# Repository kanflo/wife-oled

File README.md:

**Wife OLED**
==========

I wanted a display showing the current outside temperature alongside with the forecasted temperature in 8 hours.

The device subscribes to the topics `home/temperature/outside` and `home/temperature/forecast` displaying them in the left and right part of the display respectively. For readability I use a large font, [Ubuntu Condensed](http://font.ubuntu.com/#charset-condensed) in sizes 32px and 28px.

**Building**

Clone this repo:

```
git clone https://github.com/kanflo/wife-oled.git
cd wife-oled
git submodule init && git submodule update

```

Set the SSID configuration of EOR by adding the following to the file ```esp-open-rtos/include/private_ssid_config.h```:

```
#define WIFI_SSID "my ssid"
#define WIFI_PASS "my password"
```

Configure the MQTT stuff in ```mqtt_config.h```

Now ```make``` and ```make flash```

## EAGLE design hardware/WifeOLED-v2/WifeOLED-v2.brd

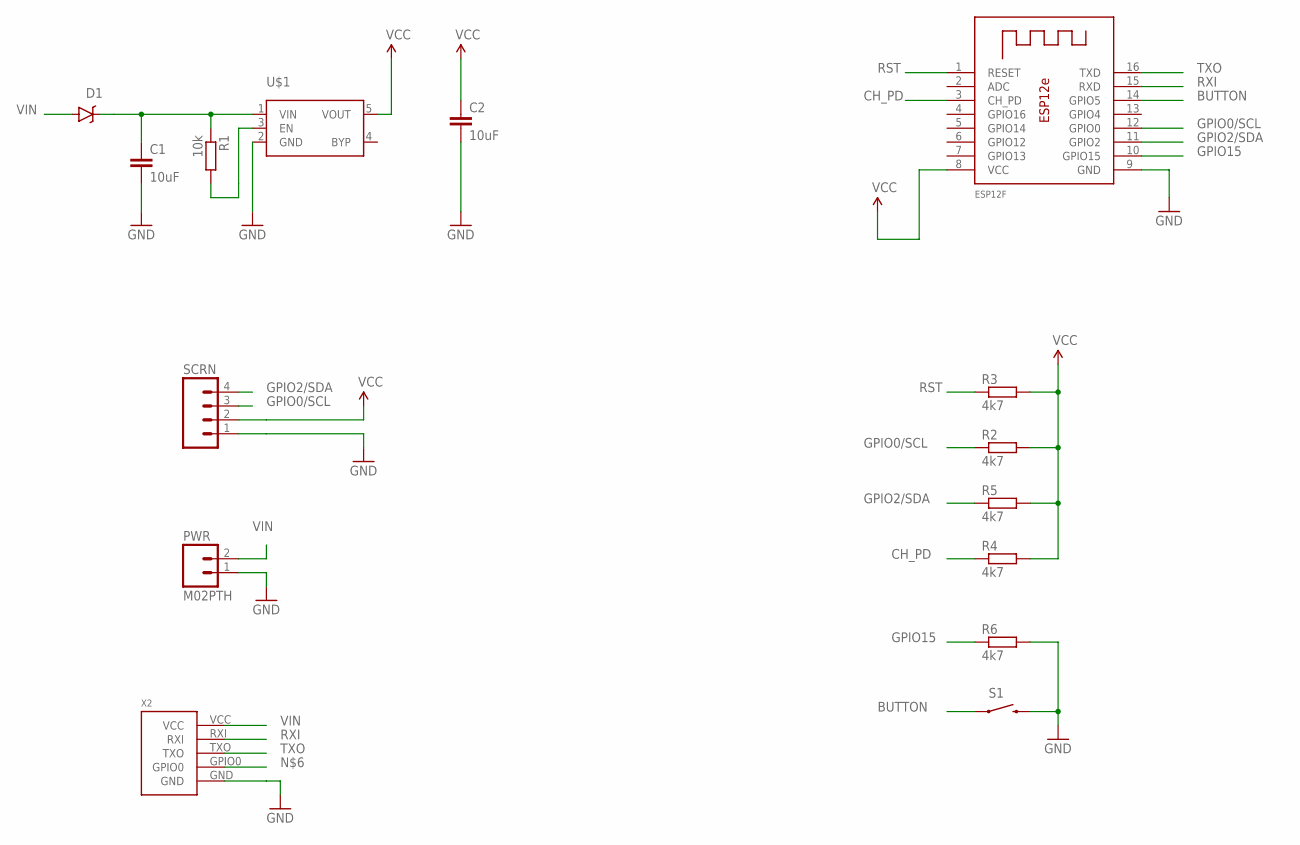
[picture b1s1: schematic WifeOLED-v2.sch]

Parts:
C1, C2: 10uF; 0603-CAP
D1: DIODE-SCHOTTKYSOD-123FL; SOD-123FL
ESP12F: ESP-12E
PWR: M02PTH; 1X02
R1: 10k; R0603
R2, R3, R4, R5, R6: 4k7; R0603
S1: SWITCH-MOMENTARY-2SMD-1101NE; TACTILE-SWITCH-1101NE
SCRN: M04PTH; 1X04
U$1: SPX3819; SOT23-5
X2: ESPROGESPROG-DEVICE; ESPROG

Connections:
BUTTON: ESP12F.14 (GPIO5), S1.1
CH_PD: ESP12F.3 (CH_PD), R4.1
GND: C1.2, C2.2, ESP12F.9 (GND), PWR.1, R6.2, S1.2, SCRN.1, U$1.2 (GND), X2.GND
GPIO0/SCL: ESP12F.12 (GPIO0), R2.1, SCRN.3
GPIO2/SDA: ESP12F.11 (GPIO2), R5.1, SCRN.4
GPIO15: ESP12F.10 (GPIO15), R6.1
unnamed: R1.2, U$1.3 (EN)
unnamed: C1.1, D1.C, R1.1, U$1.1 (VIN)
RST: ESP12F.1 (RESET), R3.1
RXI: ESP12F.15 (RXD), X2.RXI
TXO: ESP12F.16 (TXD), X2.TXO
VCC: C2.1, ESP12F.8 (VCC), R2.2, R3.2, R4.2, R5.2, SCRN.2, U$1.5 (VOUT)
VIN: D1.A, PWR.2, X2.VCC

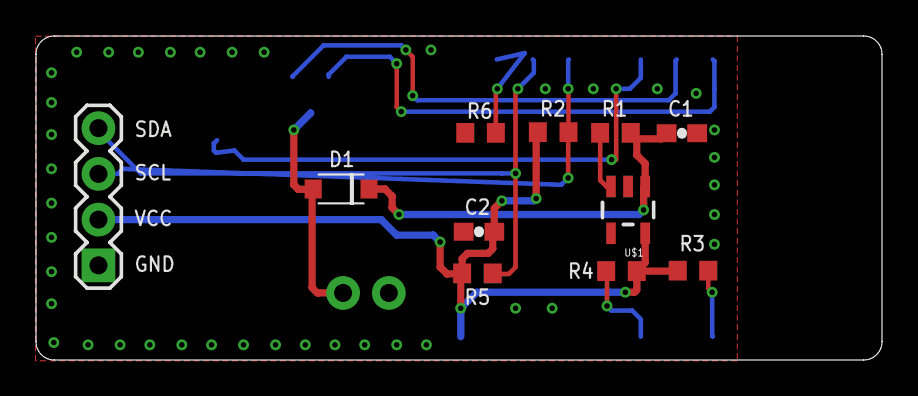
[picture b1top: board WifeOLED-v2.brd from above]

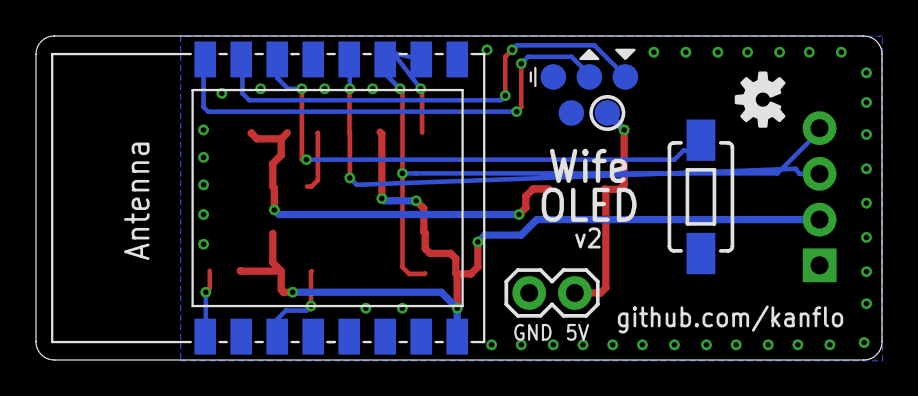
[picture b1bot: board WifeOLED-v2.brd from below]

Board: 2 copper layers, 47.0 x 18.0 mm, 16 parts (5 on the bottom side), 13 nets.

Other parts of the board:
U$2: OSHW-LOGO-S

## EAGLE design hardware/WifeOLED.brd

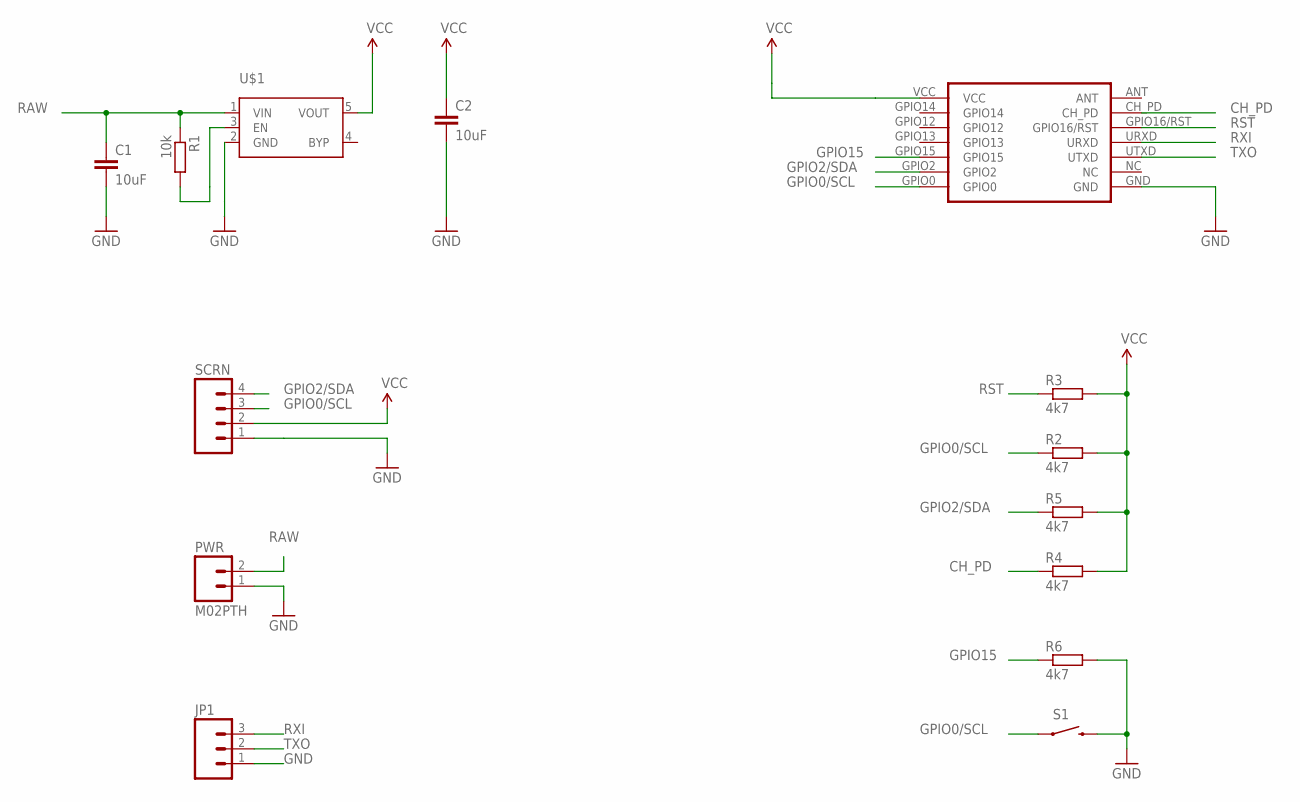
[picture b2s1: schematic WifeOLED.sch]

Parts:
C1, C2: 10uF; 0603-CAP
ESP-1: ESP-03
JP1: M03PTH; 1X03
PWR: M02PTH; 1X02
R1: 10k; R0603
R2, R3, R4, R5, R6: 4k7; R0603
S1: SWITCH-MOMENTARY-2SMD-1101NE; TACTILE-SWITCH-1101NE
SCRN: M04PTH; 1X04
U$1: SPX3819; SOT23-5

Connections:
CH_PD: ESP-1.CH_PD, R4.1
GND: C1.2, C2.2, ESP-1.GND, JP1.1, PWR.1, R6.2, S1.2, SCRN.1, U$1.2 (GND)
GPIO0/SCL: ESP-1.GPIO0, R2.1, S1.1, SCRN.3
GPIO2/SDA: ESP-1.GPIO2, R5.1, SCRN.4
GPIO15: ESP-1.GPIO15, R6.1
unnamed: R1.2, U$1.3 (EN)
RAW: C1.1, PWR.2, R1.1, U$1.1 (VIN)
RST: ESP-1.GPIO16/RST, R3.1
RXI: ESP-1.URXD, JP1.3
TXO: ESP-1.UTXD, JP1.2
VCC: C2.1, ESP-1.VCC, R2.2, R3.2, R4.2, R5.2, SCRN.2, U$1.5 (VOUT)

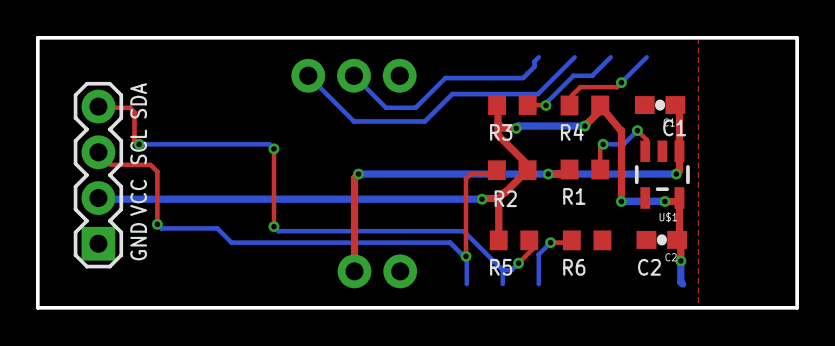
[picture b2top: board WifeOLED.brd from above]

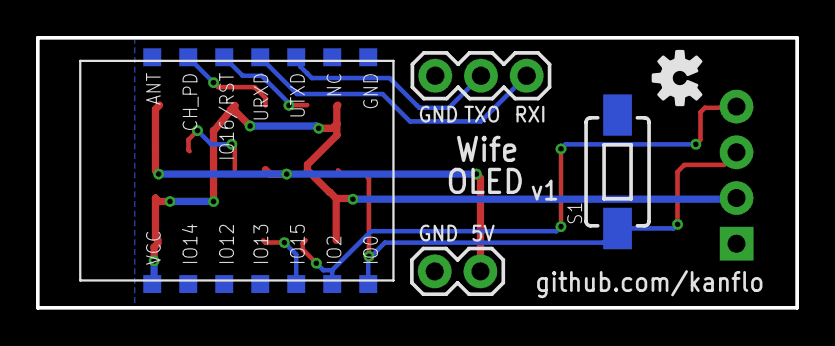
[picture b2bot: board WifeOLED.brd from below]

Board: 2 copper layers, 42.2 x 15.0 mm, 15 parts (5 on the bottom side), 11 nets.

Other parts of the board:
U$2: OSHW-LOGO-S

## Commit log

2015-07-06 Initial commit.
2015-08-30 Added gitignore
2015-08-30 Changed license from MIT to GPL.
2015-08-30 Added script for pulling weather forecasts.
2015-08-30 Added schematics and gerbers.
2015-08-30 Added stuff to .gitignore
2016-06-26 Updated to API version 2.
2016-07-23 Renamed eagle -> hardware
2016-07-23 Moved eagle stuff into v1 directory
2016-07-23 Wife OLED version 2 using ESP-12 instead of ESP-03
2016-12-27 Added pip install guides for possible missing modules
2019-12-10 Complete rewrite for ESP Open RTOS
2019-12-11 Finally did bringup of v2, found an issue. Only took ~3.5yrs...
2019-12-11 Tried to make wifi reconnects more stable, added gpio button handler
2019-12-11 Convert MAC address in more readable form
2019-12-11 Fixed snprintf:s
2019-12-11 Removed unused variables
2019-12-11 Added idiota support
2019-12-11 Fixed spelling
2019-12-11 Added idiota to app
2019-12-11 Fixed comment
2019-12-11 Added mqtt message docs

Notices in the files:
parts and their libraries:
SparkFun-Connectors: Licensing: Creative Commons ShareAlike 4.0 International - https://creativecommons.org/licenses/by-sa/4.0
